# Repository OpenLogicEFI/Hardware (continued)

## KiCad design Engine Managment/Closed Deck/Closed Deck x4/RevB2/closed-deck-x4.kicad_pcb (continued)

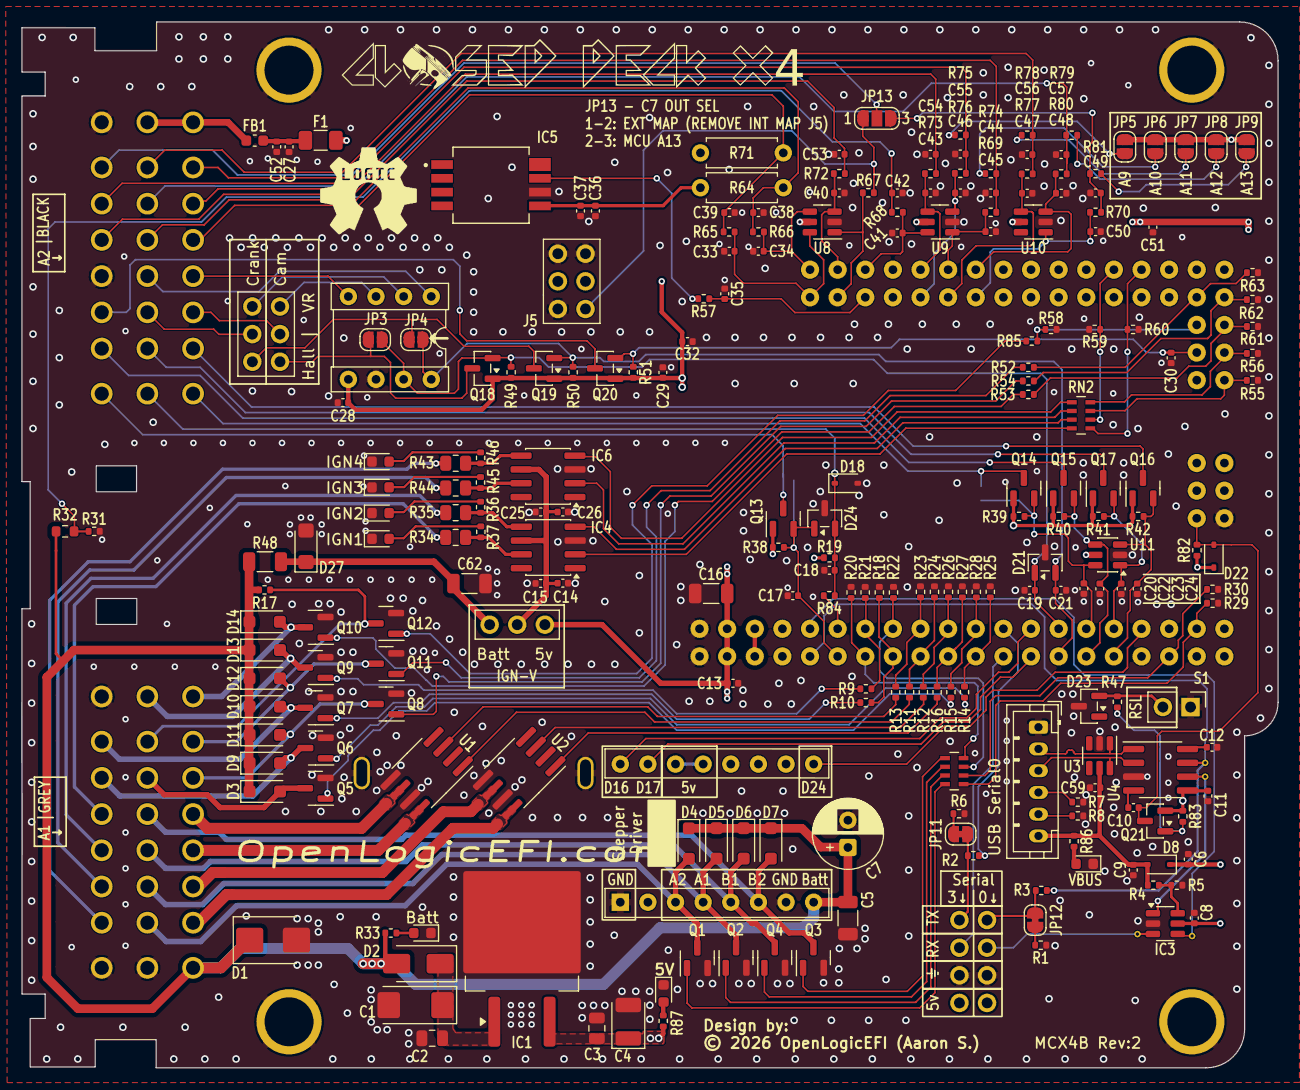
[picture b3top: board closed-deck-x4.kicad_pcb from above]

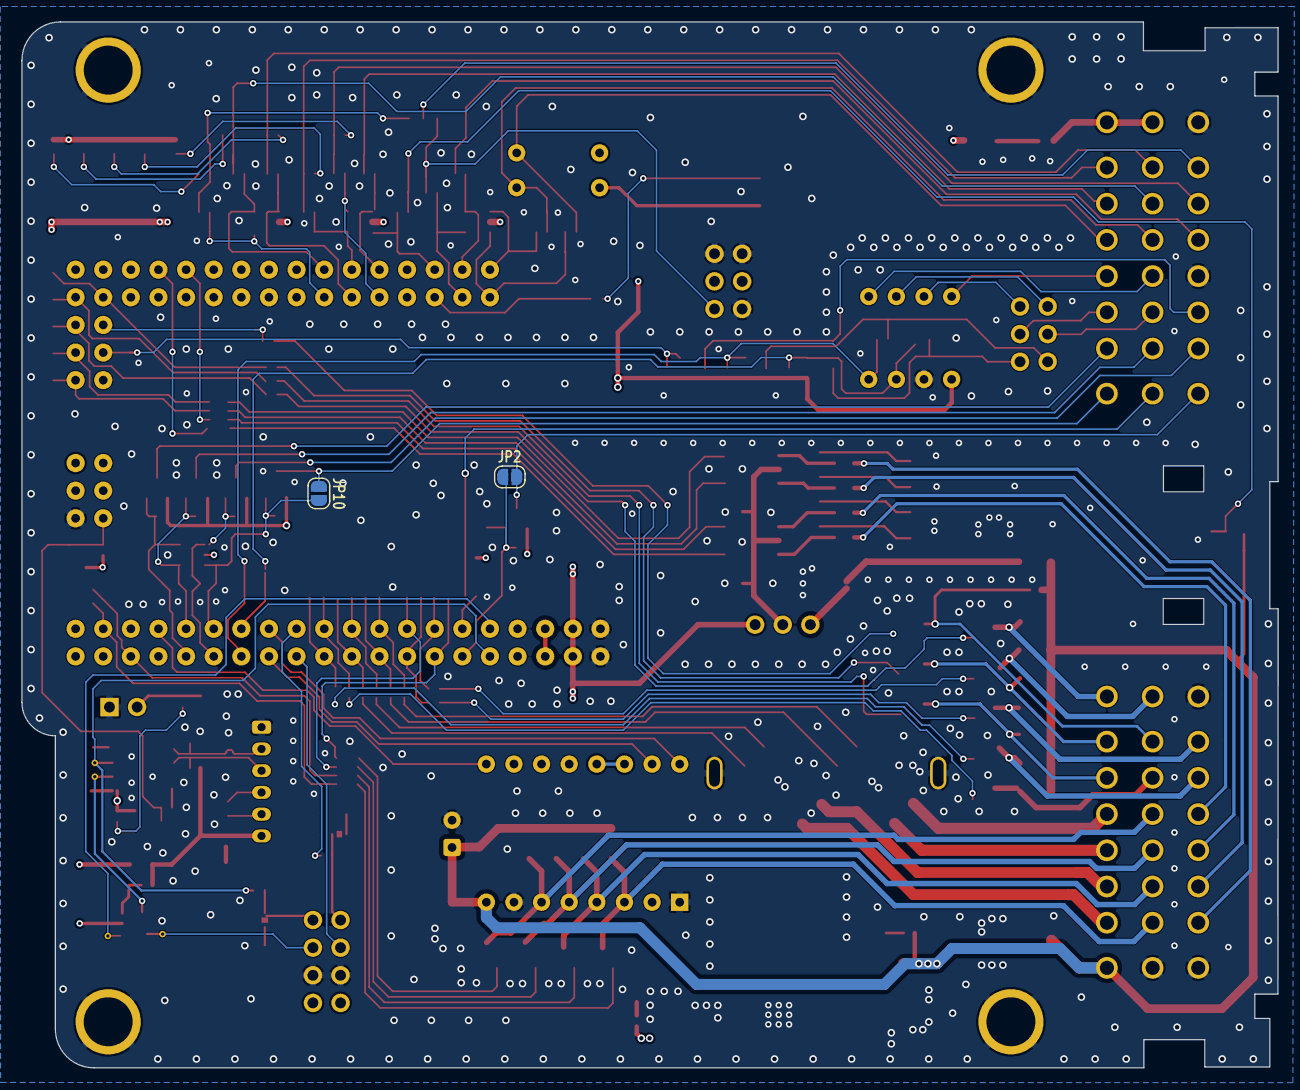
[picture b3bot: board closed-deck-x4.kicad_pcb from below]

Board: 4 copper layers, 115.5 x 96.2 mm, 243 parts (2 on the bottom side), 158 nets.

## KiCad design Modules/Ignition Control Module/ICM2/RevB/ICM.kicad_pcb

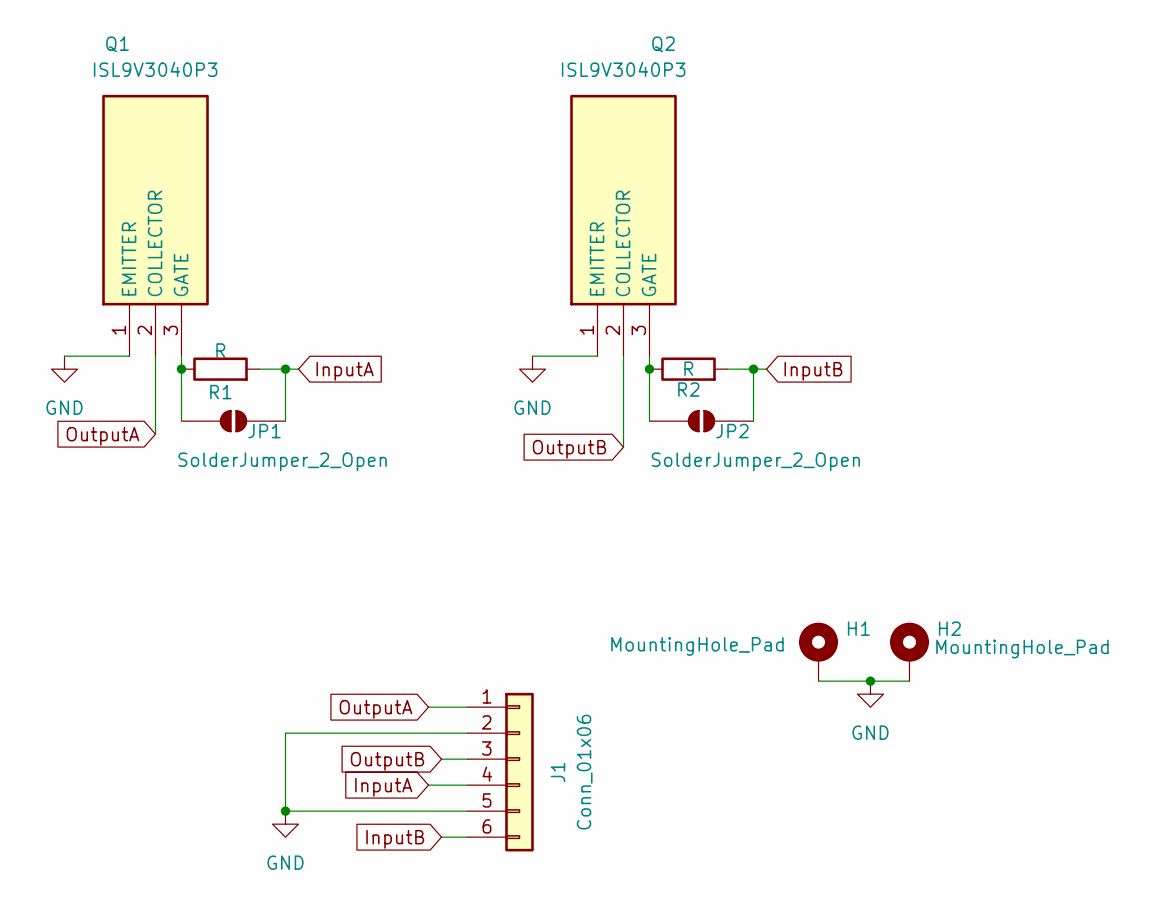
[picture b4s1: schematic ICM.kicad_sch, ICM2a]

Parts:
H1, H2: MountingHole_Pad; MountingHole_3.2mm_M3_DIN965_Pad_TopBottom
J1: Conn_01x06; Molex_Mini-Fit_Jr_5569-06A2_2x03_P4.20mm_Horizontal
JP1, JP2: SolderJumper_2_Open; SolderJumper-2_P1.3mm_Bridged_RoundedPad1.0x1.5mm
Q1, Q2: ISL9V3040P3; TO-252-2-frontThermalOnly; Manufacturer_Part_Number ISL9V3040P3; Mouser Part Number 512-ISL9V3040P3
R1, R2: R; R_Axial_DIN0207_L6.3mm_D2.5mm_P10.16mm_Horizontal

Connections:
GND: H1.1 (1_1), H2.1 (1_1), J1.2, J1.5, Q1.1 (EMITTER), Q2.1 (EMITTER)
InputA: J1.4, JP1.2 (B), R1.2
InputB: J1.6, JP2.2 (B), R2.2
unnamed: JP1.1 (A), Q1.3 (GATE), R1.1
unnamed: JP2.1 (A), Q2.3 (GATE), R2.1
OutputA: J1.1, Q1.2 (COLLECTOR)
OutputB: J1.3, Q2.2 (COLLECTOR)

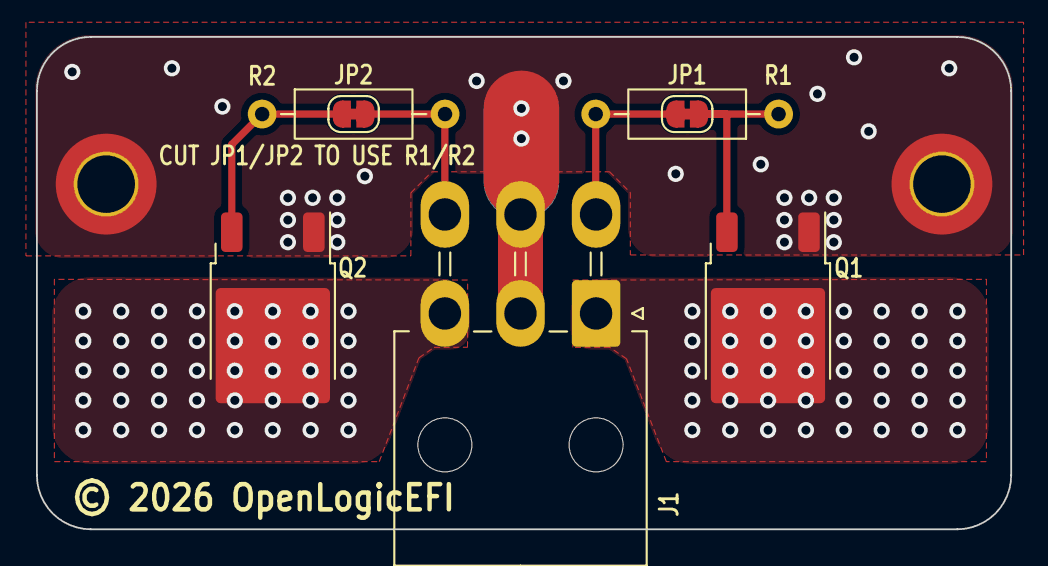
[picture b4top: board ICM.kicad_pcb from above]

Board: 2 copper layers, 54.1 x 27.4 mm, 9 parts (0 on the bottom side), 7 nets.

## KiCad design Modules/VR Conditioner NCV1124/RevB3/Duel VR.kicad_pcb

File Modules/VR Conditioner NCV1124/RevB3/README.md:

# VR Conditioner
Based on the NCV1124
RevB3

Changes:
*Layout improvements

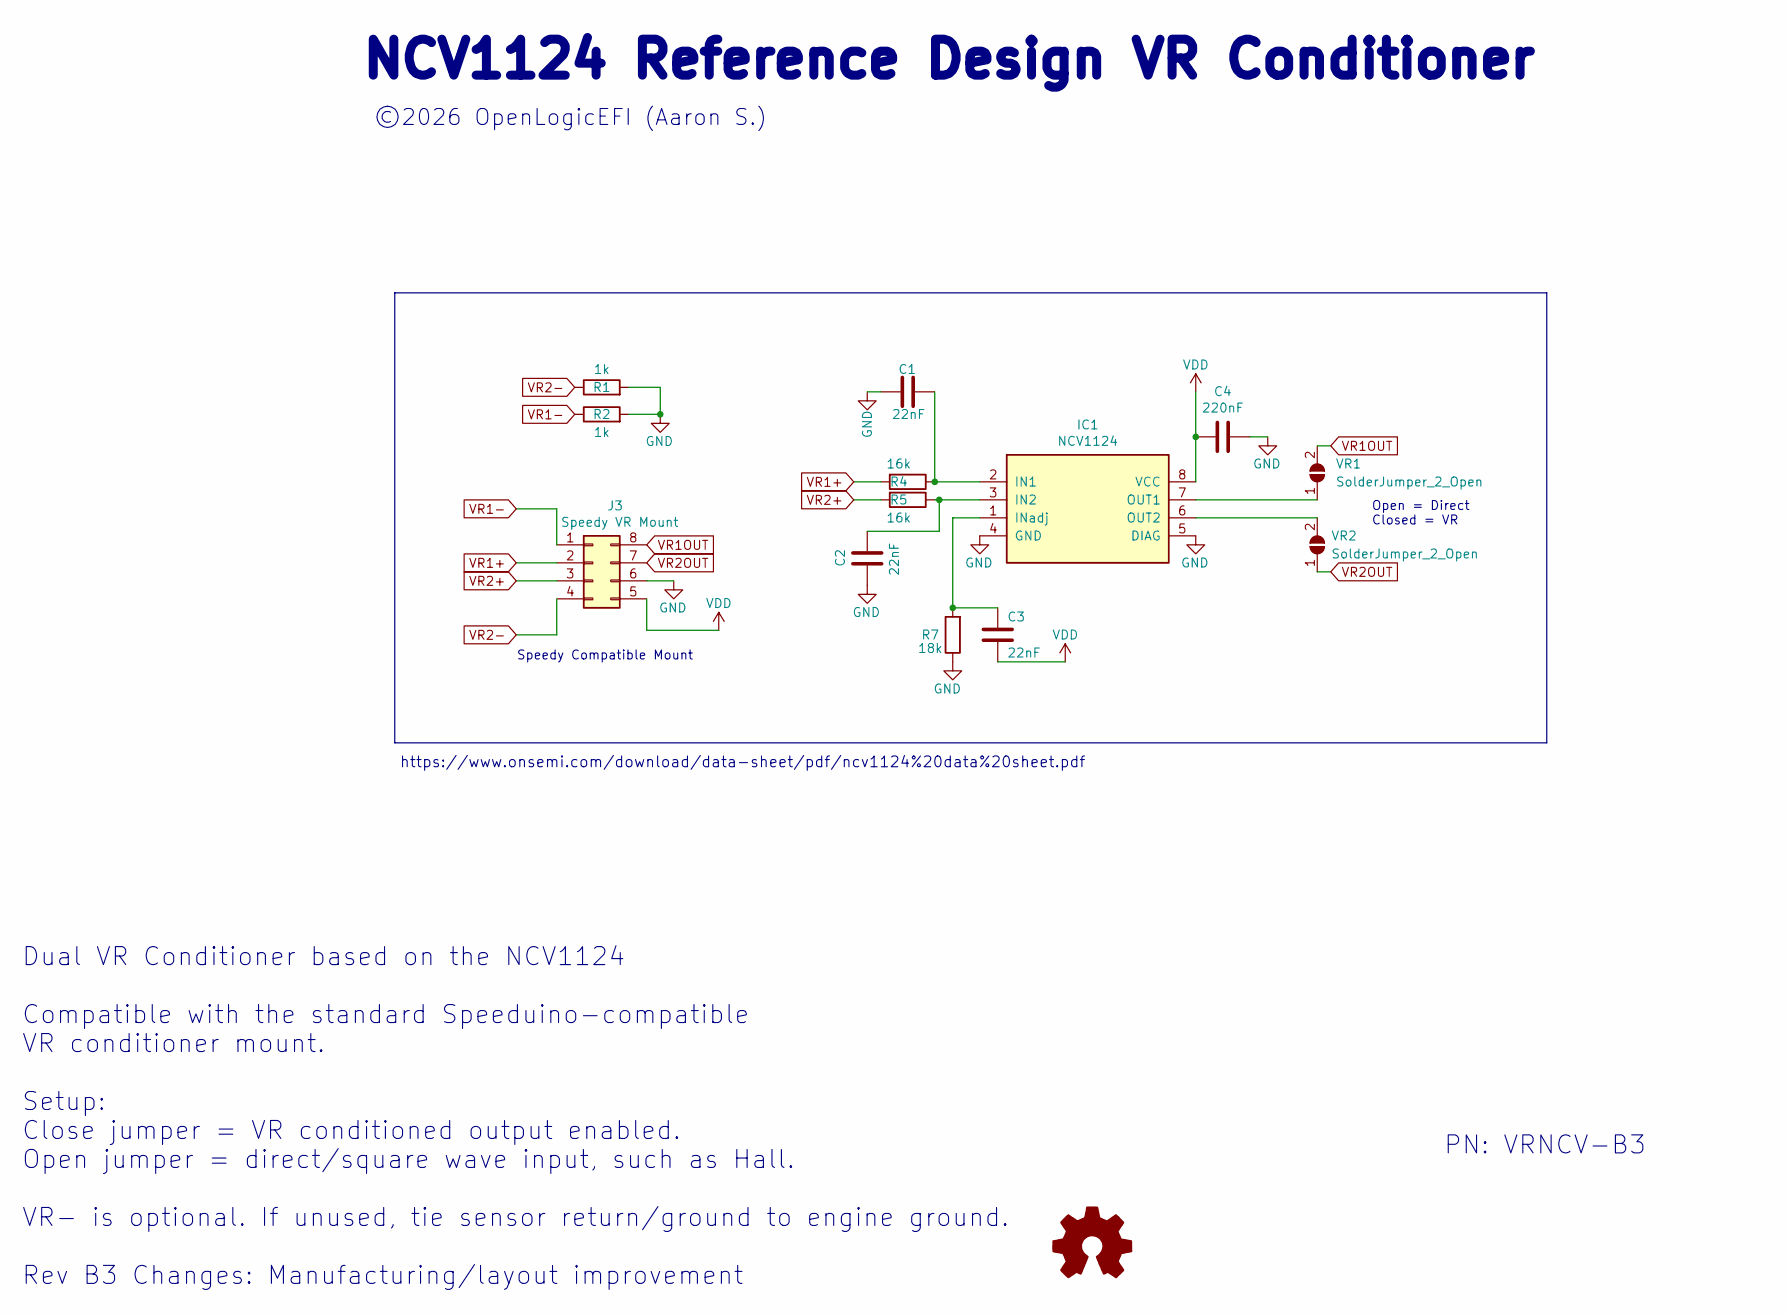
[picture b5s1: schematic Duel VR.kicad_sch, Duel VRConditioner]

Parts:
C1, C2, C3: 22nF; C_0603_1608Metric; LCSC C21122
C4: 220nF; C_0603_1608Metric; LCSC C21120
G1: Logo_Open_Hardware_Small; SpeeduinoCompatible-14mm
IC1: NCV1124; SO-8_3.9x4.9mm_P1.27mm
J3: Speedy VR Mount; DIP-8_W7.62mm_Socket_VRConditioner
R1, R2: 1k; R_1206_3216Metric; LCSC C4410
R4, R5: 16k; R_1210_3225Metric; LCSC C3013274
R7: 18k; R_0603_1608Metric; LCSC C25810
VR1, VR2: SolderJumper_2_Open; SolderJumper-2_P1.3mm_Open_RoundedPad1.0x1.5mm

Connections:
GND: C1.1, C2.2, C4.2, IC1.4 (GND), IC1.5 (DIAG), J3.6, R1.2, R2.2, R7.1
unnamed: C1.2, IC1.2 (IN1), R4.1
unnamed: C2.1, IC1.3 (IN2), R5.1
unnamed: C3.1, IC1.1 (INadj), R7.2
unnamed: IC1.7 (OUT1), VR1.1 (A)
unnamed: IC1.6 (OUT2), VR2.2 (B)
VDD: C3.2, C4.1, IC1.8 (VCC), J3.5
VR1+: J3.2, R4.2
VR1-: J3.1, R2.1
VR1OUT: J3.8, VR1.2 (B)
VR2+: J3.3, R5.2
VR2-: J3.4, R1.1
VR2OUT: J3.7, VR2.1 (A)

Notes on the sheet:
https://www.onsemi.com/download/data-sheet/pdf/ncv1124%20data%20sheet.pdf
Dual VR Conditioner based on the NCV1124 Compatible with the standard Speeduino-compatible VR conditioner mount. Setup: Close jumper = VR conditioned output enabled. Open jumper = direct/square wave input, such as Hall. VR- is optional. If unused, tie sensor return/ground to engine ground. Rev B3 C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
NCV1124 Reference Design VR Conditioner
©2026 OpenLogicEFI (Aaron S.)
Open = Direct Closed = VR
Speedy Compatible Mount
PN: VRNCV-B3

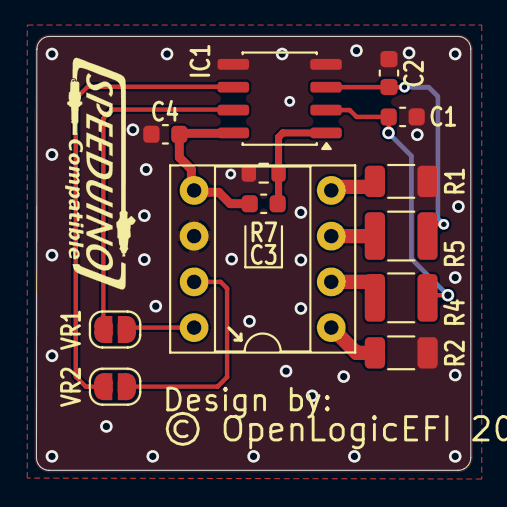
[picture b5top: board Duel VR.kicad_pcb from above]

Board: 2 copper layers, 24.1 x 24.1 mm, 14 parts (0 on the bottom side), 13 nets.

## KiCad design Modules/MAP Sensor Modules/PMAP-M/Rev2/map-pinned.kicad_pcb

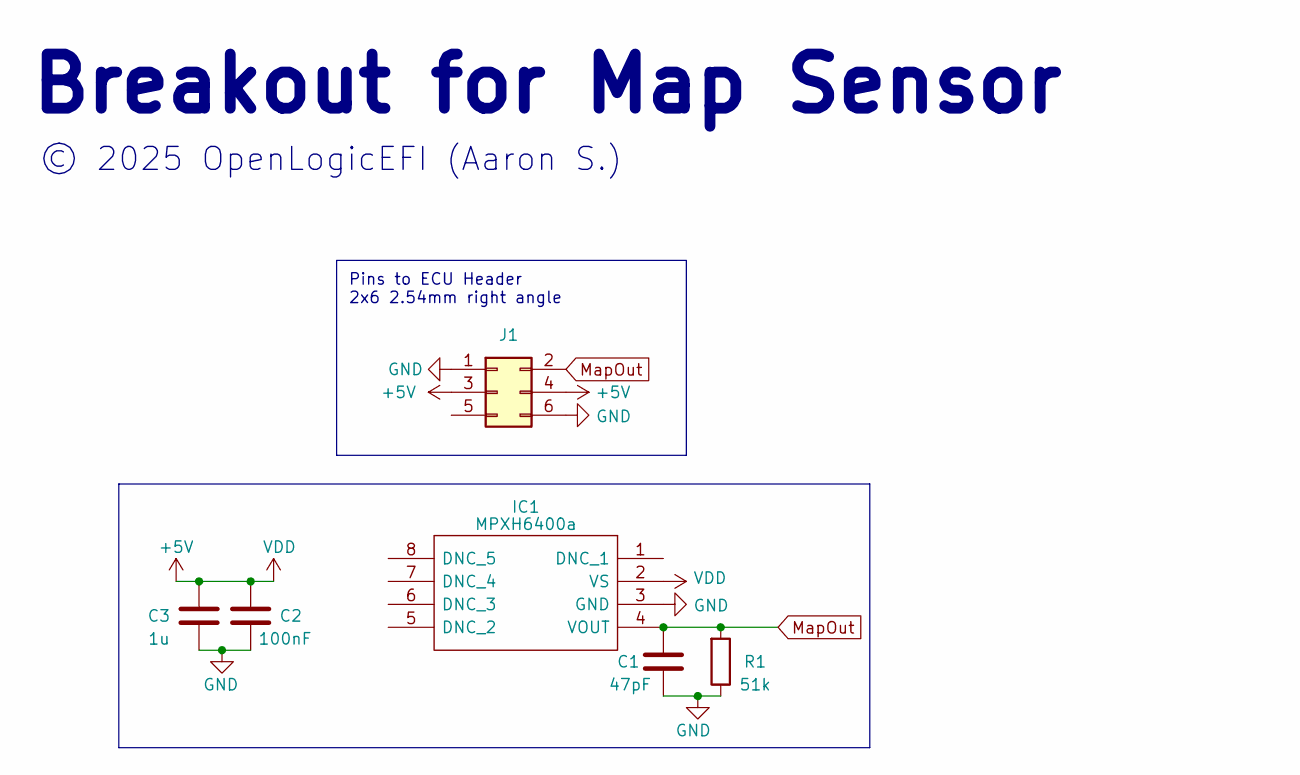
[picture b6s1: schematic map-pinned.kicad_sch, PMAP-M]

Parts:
C1: 47pF; C_0402_1005Metric; Manufacture Part Number 0402CG470J500NT; LCSC C1567
C2: 100nF; C_0402_1005Metric; Manufacture Part Number CL05B104KO5NNNC; LCSC C1525
C3: 1u; C_0805_2012Metric; Manufacture Part Number CL21B105KBFNNNE; LCSC C28323
IC1: MPXH6400a; MPXHxxx_Handsoldering
J1: Conn_02x03_Odd_Even; PinHeader_2x03_P2.54mm_Horizontal
R1: 51k; R_0402_1005Metric; Manufacture Part Number 0402WGF5102TCE; LCSC C25794

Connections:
+5V: C2.1, C3.1, IC1.2 (VS), J1.3, J1.4
GND: C1.2, C2.2, C3.2, IC1.3 (GND), J1.1, J1.6, R1.1
MapOut: C1.1, IC1.4 (VOUT), J1.2, R1.2

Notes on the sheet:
Pins to ECU Header 2x6 2.54mm right angle
© 2025 OpenLogicEFI (Aaron S.)
Breakout for Map Sensor

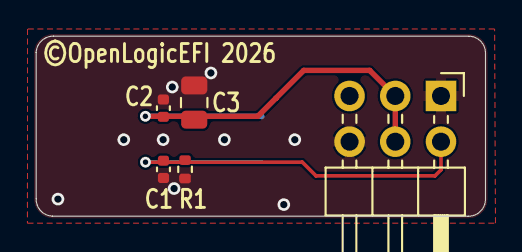
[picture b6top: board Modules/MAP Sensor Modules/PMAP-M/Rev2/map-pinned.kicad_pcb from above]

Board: 2 copper layers, 25.0 x 10.0 mm, 6 parts (1 on the bottom side), 3 nets.

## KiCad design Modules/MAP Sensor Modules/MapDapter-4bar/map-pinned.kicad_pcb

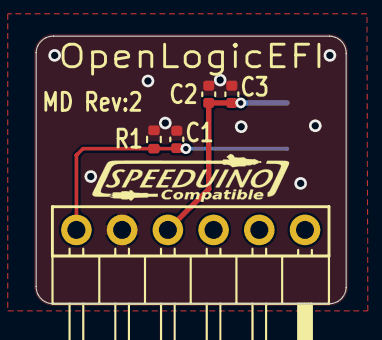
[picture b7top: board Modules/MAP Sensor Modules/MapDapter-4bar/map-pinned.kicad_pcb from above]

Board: 2 copper layers, 17.2 x 14.9 mm, 6 parts (1 on the bottom side), 3 nets.

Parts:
C1: 47pF; C_0402_1005Metric
C2: 100nF; C_0402_1005Metric
C3: 1u; C_0402_1005Metric
IC1: MPXH6400a; MPXHxxx_Handsoldering
J2: Conn_01x06; MapDapter_1x06_P2.54mm_Horizontal
R1: 51k; R_0402_1005Metric

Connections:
+5V: C2.1, C3.1, IC1.2 (VS), J2.4
GND: C1.2, C2.2, C3.2, IC1.3 (GND), J2.5, R1.1
MapOut: C1.1, IC1.4 (VOUT), J2.6, R1.2

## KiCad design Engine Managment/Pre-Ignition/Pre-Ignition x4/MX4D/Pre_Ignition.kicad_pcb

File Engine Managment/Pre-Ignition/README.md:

# Pre-Ignition

Pre-Ignition is a hardware shield designed to use an Arduino Mega as the central microcontroller unit (MCU), thereby enabling it to operate as a standalone engine management system. This functionality is achieved when the shield is coupled with compatible firmware from an open-source project called Speeduino, developed by Josh Stewart.

www.OpenLogicEFI.com

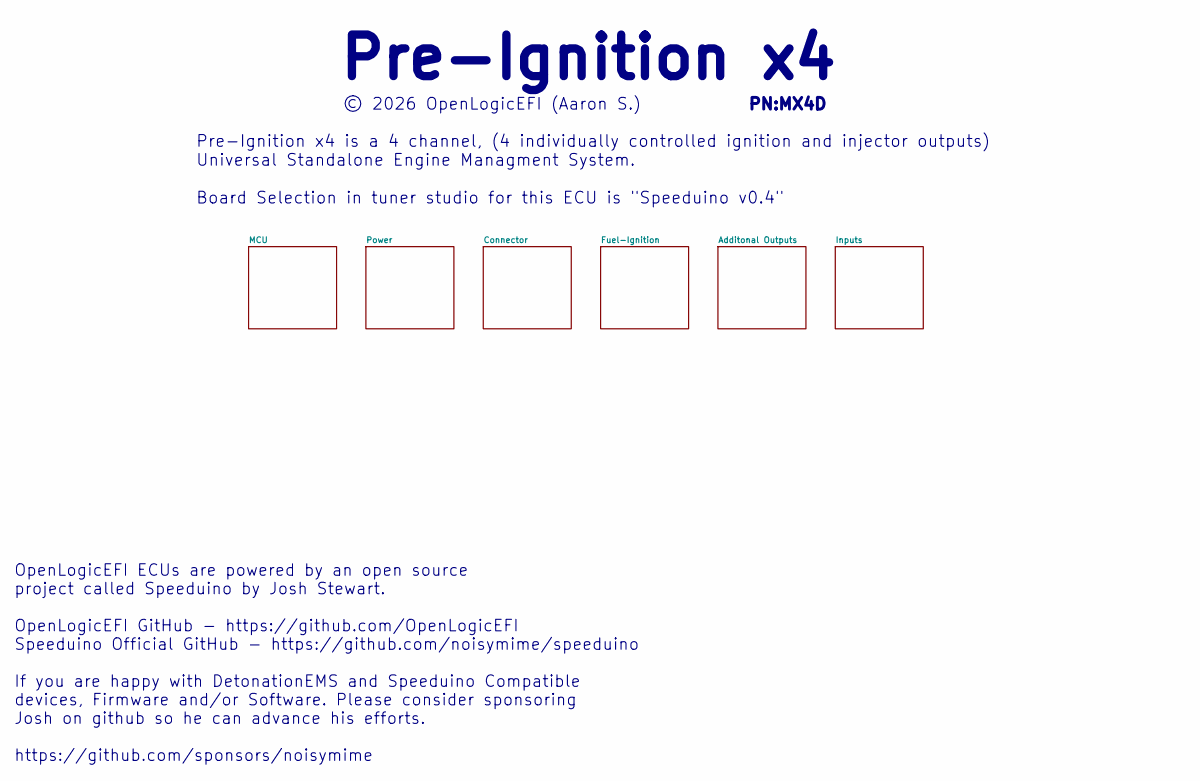
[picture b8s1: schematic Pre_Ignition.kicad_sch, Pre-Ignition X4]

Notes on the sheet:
Pre-Ignition x4 is a 4 channel, (4 individually controlled ignition and injector outputs) Universal Standalone Engine Managment System. Board Selection in tuner studio for this ECU is "Speeduino v0.4"
© 2026 OpenLogicEFI (Aaron S.)
Pre-Ignition x4
OpenLogicEFI ECUs are powered by an open source project called Speeduino by Josh Stewart. OpenLogicEFI GitHub - https://github.com/OpenLogicEFI Speeduino Official GitHub - https://github.com/noisymime/speeduino If you are happy with DetonationEMS and Speeduino Compatible devices, Firmware and/or So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
PN:MX4D

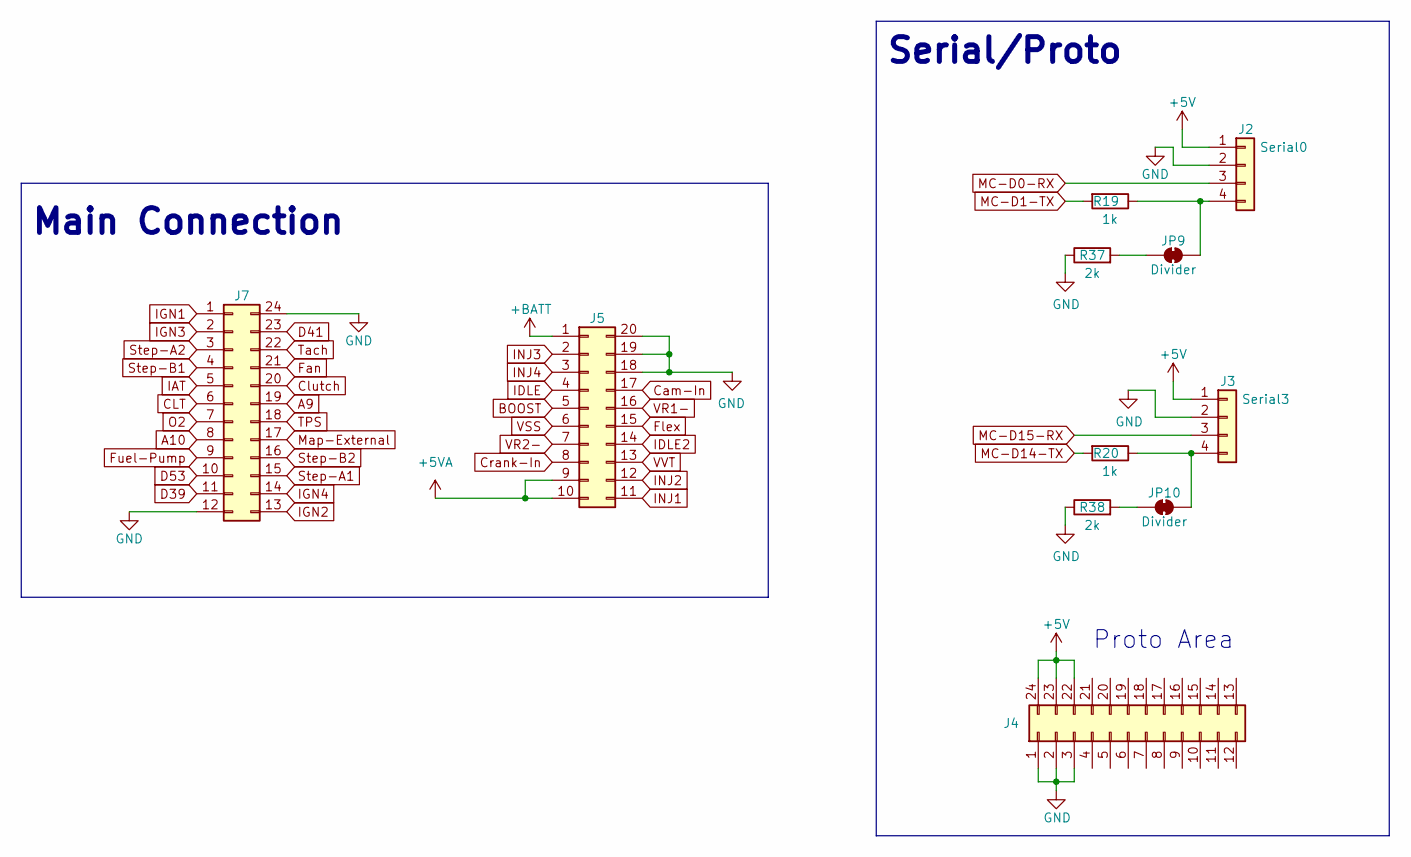
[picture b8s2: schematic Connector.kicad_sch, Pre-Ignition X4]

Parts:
J2: Serial0; 1X4-PROTO
J3: Serial3; 1X4-PROTO
J4: Conn_02x12_Counter_Clockwise; PROTO-3X8-24pin
J5: Conn_02x10_Counter_Clockwise; Molex_Micro-Fit_3.0_43045-2000_2x10_P3.00mm_Horizontal
J7: Conn_02x12_Counter_Clockwise; Molex_Micro-Fit_3.0_43045-2400_2x12_P3.00mm_Horizontal
JP9, JP10: Divider; SolderJumper-2_P1.3mm_Bridged_RoundedPad1.0x1.5mm
R19, R20: 1k; R_0402_1005Metric; Manufacture Part Number 0402WGF1001TCE; LCSC C11702
R37, R38: 2k; R_0603_1608Metric; LCSC C22975

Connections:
+5V: J2.1, J3.1, J4.22, J4.23, J4.24; also elsewhere on the board
+5VA: J5.9, J5.10; also elsewhere on the board
+BATT: J5.1; also elsewhere on the board
A9: J7.19; also elsewhere on the board
A10: J7.8; also elsewhere on the board
BOOST: J5.5; also elsewhere on the board
CLT: J7.6; also elsewhere on the board
Cam-In: J5.17; also elsewhere on the board
Clutch: J7.20; also elsewhere on the board
Crank-In: J5.8; also elsewhere on the board
D39: J7.11; also elsewhere on the board
D41: J7.23; also elsewhere on the board
D53: J7.10; also elsewhere on the board
Fan: J7.21; also elsewhere on the board
Flex: J5.15; also elsewhere on the board
Fuel-Pump: J7.9; also elsewhere on the board
GND: J2.2, J3.2, J4.1, J4.2, J4.3, J5.18, J5.19, J5.20, J7.12, J7.24, R37.1, R38.1; also elsewhere on the board
IAT: J7.5; also elsewhere on the board
IDLE: J5.4; also elsewhere on the board
IDLE2: J5.14; also elsewhere on the board
IGN1: J7.1; also elsewhere on the board
IGN2: J7.13; also elsewhere on the board
IGN3: J7.2; also elsewhere on the board
IGN4: J7.14; also elsewhere on the board
INJ1: J5.11; also elsewhere on the board
INJ2: J5.12; also elsewhere on the board
INJ3: J5.2; also elsewhere on the board
INJ4: J5.3; also elsewhere on the board
MC-D0-RX: J2.3; also elsewhere on the board
MC-D1-TX: R19.2; also elsewhere on the board
MC-D14-TX: R20.2; also elsewhere on the board
MC-D15-RX: J3.3; also elsewhere on the board
Map-External: J7.17; also elsewhere on the board
unnamed: J2.4, JP9.2 (B), R19.1
unnamed: J3.4, JP10.2 (B), R20.1
unnamed: JP9.1 (A), R37.2
unnamed: JP10.1 (A), R38.2
O2: J7.7; also elsewhere on the board
Step-A1: J7.15; also elsewhere on the board
Step-A2: J7.3; also elsewhere on the board
Step-B1: J7.4; also elsewhere on the board
Step-B2: J7.16; also elsewhere on the board
TPS: J7.18; also elsewhere on the board
Tach: J7.22; also elsewhere on the board
VR1-: J5.16; also elsewhere on the board
VR2-: J5.7; also elsewhere on the board
VSS: J5.6; also elsewhere on the board
VVT: J5.13; also elsewhere on the board

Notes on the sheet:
Proto Area
Serial/Proto
Main Connection

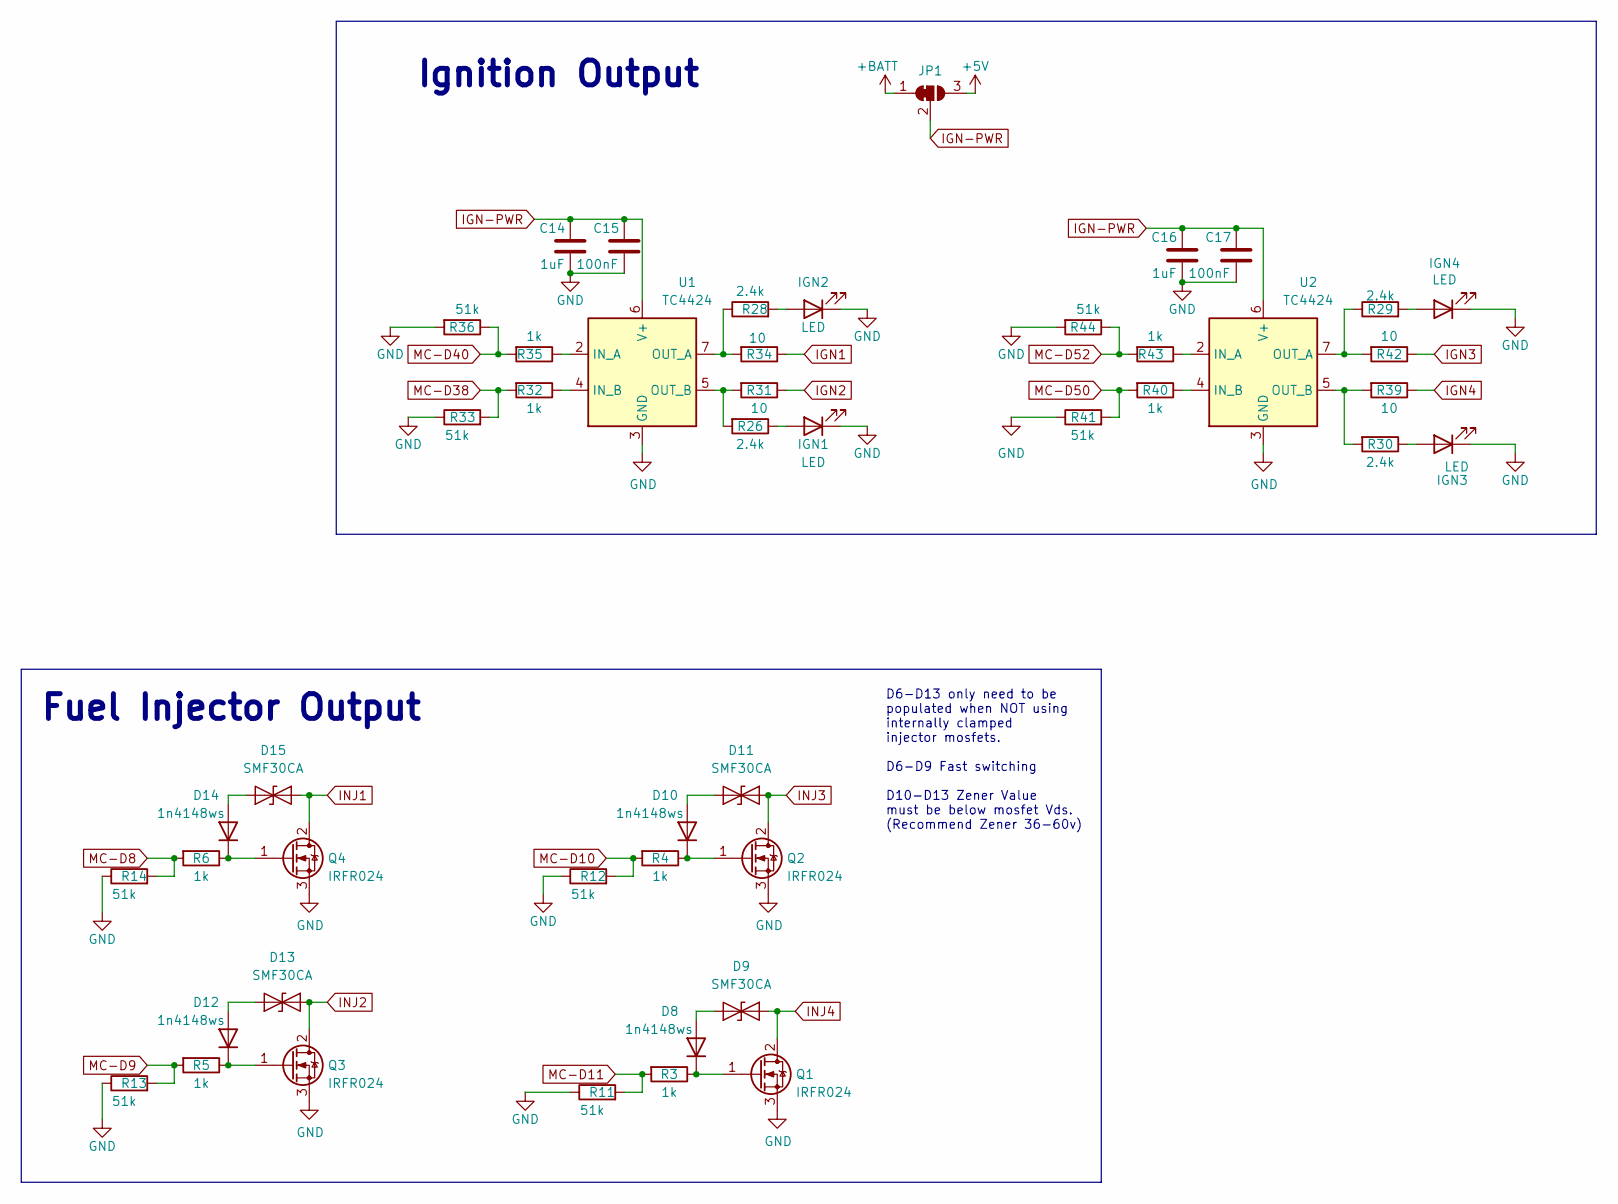
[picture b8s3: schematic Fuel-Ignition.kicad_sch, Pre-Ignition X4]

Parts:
C14, C16: 1uF; C_0603_1608Metric; LCSC C15849
C15, C17: 100nF; C_0603_1608Metric; LCSC C14663
D8, D10, D12, D14: 1n4148ws; D_SOD-323F; LCSC C2128
D9, D11, D13, D15: SMF30CA; D_SOD-123F; LCSC C19077519
IGN1, IGN2, IGN3, IGN4: LED; LED_0603_1608Metric; LCSC C2286
JP1: SolderJumper_3_Bridged12; 1x03_Horizontal_2.54mm
Q1, Q2, Q3, Q4: IRFR024; TO-252-2; LCSC C2583
R3, R4, R5, R6, R32, R35, R40, R43: 1k; R_0402_1005Metric; Manufacture Part Number 0402WGF1001TCE; LCSC C11702
R11, R12, R13, R14, R33, R36, R41, R44: 51k; R_0402_1005Metric; Manufacture Part Number 0402WGF5102TCE; LCSC C25794
R26, R28, R29, R30: 2.4k; C_0603_1608Metric; LCSC C22940
R31, R34, R39, R42: 10; R_1206_3216Metric; LCSC C17903
U1, U2: TC4424; SOIC-8_3.9x4.9mm_P1.27mm; LCSC C2685358

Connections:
+5V: JP1.3 (B); also elsewhere on the board
+BATT: JP1.1 (A); also elsewhere on the board
GND: C14.2, C15.2, C16.2, C17.2, IGN1.1 (K), IGN2.1 (K), IGN3.1 (K), IGN4.1 (K), Q1.3 (S), Q2.3 (S), Q3.3 (S), Q4.3 (S), R11.1, R12.1, R13.1, R14.1, R33.1, R36.2, R41.1, R44.2, U1.3 (GND), U2.3 (GND); also elsewhere on the board
IGN1: R34.1; also elsewhere on the board
IGN2: R31.1; also elsewhere on the board
IGN3: R42.1; also elsewhere on the board
IGN4: R39.1; also elsewhere on the board
IGN-PWR: C14.1, C15.1, C16.1, C17.1, JP1.2 (C), U1.6 (V+), U2.6 (V+)
INJ1: D15.1 (A1), Q4.2 (D); also elsewhere on the board
INJ2: D13.1 (A1), Q3.2 (D); also elsewhere on the board
INJ3: D11.1 (A1), Q2.2 (D); also elsewhere on the board
INJ4: D9.1 (A1), Q1.2 (D); also elsewhere on the board
MC-D8: R6.2, R14.2; also elsewhere on the board
MC-D9: R5.2, R13.2; also elsewhere on the board
MC-D10: R4.2, R12.2; also elsewhere on the board
MC-D11: R3.2, R11.2; also elsewhere on the board
MC-D38: R32.2, R33.2; also elsewhere on the board
MC-D40: R35.2, R36.1; also elsewhere on the board
MC-D50: R40.2, R41.2; also elsewhere on the board
MC-D52: R43.2, R44.1; also elsewhere on the board
unnamed: D8.2 (A), D9.2 (A2)
unnamed: D8.1 (K), Q1.1 (G), R3.1
unnamed: D10.2 (A), D11.2 (A2)
unnamed: D10.1 (K), Q2.1 (G), R4.1
unnamed: D12.2 (A), D13.2 (A2)
unnamed: D12.1 (K), Q3.1 (G), R5.1
unnamed: D14.2 (A), D15.2 (A2)
unnamed: D14.1 (K), Q4.1 (G), R6.1
unnamed: IGN1.2 (A), R26.1
unnamed: IGN2.2 (A), R28.2
unnamed: IGN3.2 (A), R30.1
unnamed: IGN4.2 (A), R29.2
unnamed: R35.1, U1.2 (IN_A)
unnamed: R32.1, U1.4 (IN_B)
unnamed: R28.1, R34.2, U1.7 (OUT_A)
unnamed: R26.2, R31.2, U1.5 (OUT_B)
unnamed: R43.1, U2.2 (IN_A)
unnamed: R40.1, U2.4 (IN_B)
unnamed: R29.1, R42.2, U2.7 (OUT_A)
unnamed: R30.2, R39.2, U2.5 (OUT_B)

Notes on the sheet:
Fuel Injector Output
D6-D13 only need to be populated when NOT using internally clamped injector mosfets. D6-D9 Fast switching D10-D13 Zener Value must be below mosfet Vds. (Recommend Zener 36-60v)
Ignition Output

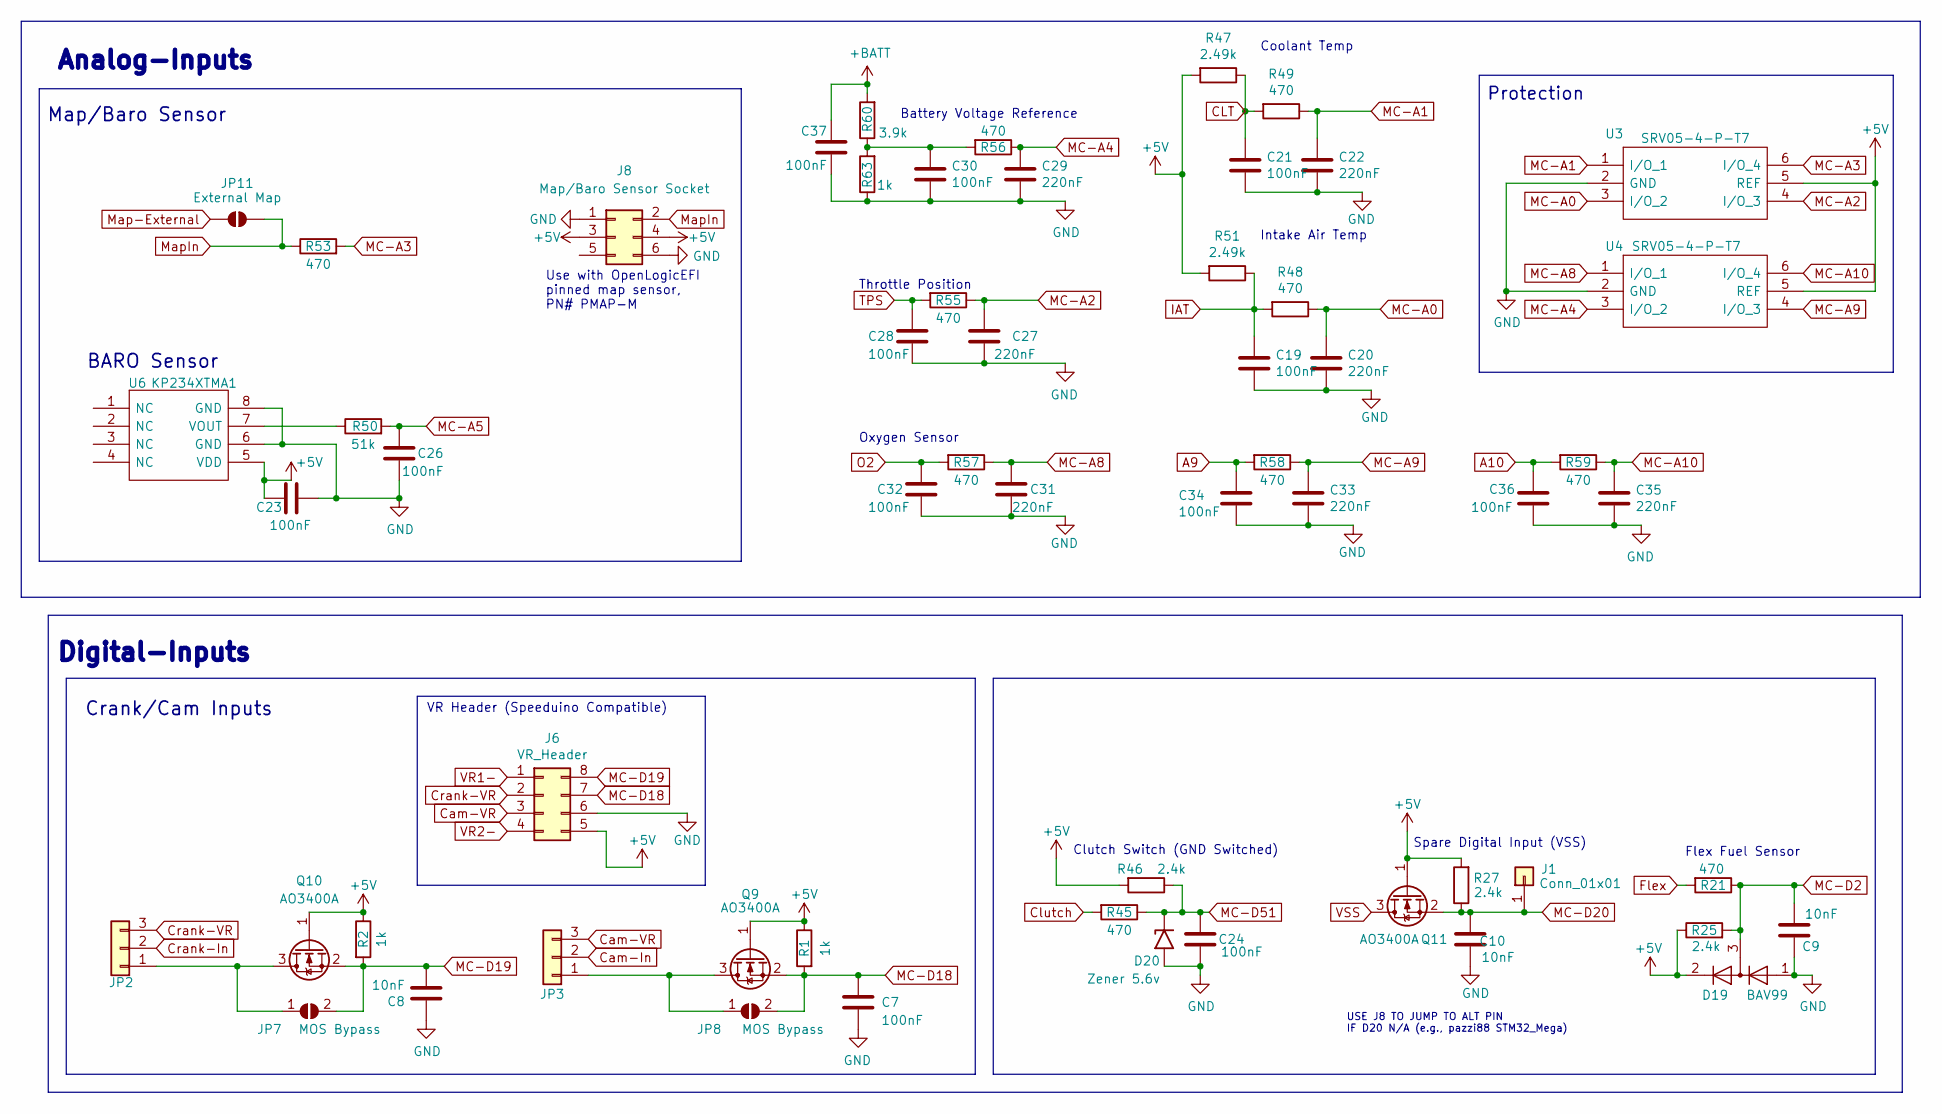
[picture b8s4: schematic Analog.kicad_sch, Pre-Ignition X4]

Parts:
C7, C19, C21, C23, C24, C26, C28, C30, C32, C34, C36, C37: 100nF; C_0603_1608Metric; LCSC C14663
C8, C9, C10: 10nF; C_0603_1608Metric; LCSC C57112
C20, C22, C27, C29, C31, C33, C35: 220nF; C_0603_1608Metric; LCSC C21120
D19: BAV99; SOT-23; LCSC C2500
D20: Zener 5.6v; D_SOD-323; Manufacture Part Number MM3Z5V6; LCSC C19077456
J1: Conn_01x01; PinSocket_1x01_P2.54mm_Vertical
J6: VR_Header; Socket_VRConditioner_Corrected
J8: Map/Baro Sensor Socket; PinSocket_2x03_P2.54mm_Vertical
JP2, JP3: Conn_01x03; 1x03-Proto
JP7, JP8: MOS Bypass; SolderJumper-2_P1.3mm_Open_RoundedPad1.0x1.5mm
JP11: External Map; SolderJumper-2_P1.3mm_Open_RoundedPad1.0x1.5mm
Q9, Q10, Q11: AO3400A; SOT-23; LCSC C20917
R1, R2, R63: 1k; R_0402_1005Metric; Manufacture Part Number 0402WGF1001TCE; LCSC C11702
R21, R45, R48, R49, R53, R55, R56, R57, R58, R59: 470; R_0603_1608Metric; LCSC C23179
R25: 2.4k; C_0603_1608Metric; LCSC C22940
R27, R46: 2.4k; C_0603_1608Metric; Manufacture Part Number 0402WGF1001TCE; LCSC C22940
R47, R51: 2.49k; R_Axial_DIN0207_L6.3mm_D2.5mm_P7.62mm_Horizontal
R50: 51k; R_0402_1005Metric; Manufacture Part Number 0402WGF5102TCE; LCSC C25794
R60: 3.9k; R_0603_1608Metric; LCSC C23018
U3, U4: SRV05-4-P-T7; SOT-23-6; LCSC C85364
U6: KP234XTMA1; KP234-Handsoldering

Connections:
+5V: C23.2, D19.2 (A), J6.5, J8.3, J8.4, Q9.1 (G), Q10.1 (G), Q11.1 (G), R1.1, R2.1, R25.1, R27.2, R46.2, R47.2, R51.2, U3.5 (REF), U4.5 (REF), U6.5 (VDD); also elsewhere on the board
+BATT: C37.1, R60.2; also elsewhere on the board
A9: C34.1, R58.2; also elsewhere on the board
A10: C36.1, R59.2; also elsewhere on the board
CLT: C21.1, R47.1, R49.2; also elsewhere on the board
Cam-In: JP3.2; also elsewhere on the board
Cam-VR: J6.3, JP3.3
Clutch: R45.2; also elsewhere on the board
Crank-In: JP2.2; also elsewhere on the board
Crank-VR: J6.2, JP2.3
Flex: R21.2; also elsewhere on the board
GND: C7.1, C8.1, C9.2, C10.2, C19.2, C20.2, C21.2, C22.2, C23.1, C24.2, C26.1, C27.2, C28.2, C29.2, C30.2, C31.2, C32.2, C33.2, C34.2, C35.2, C36.2, C37.2, D19.1 (K), D20.2 (A2), J6.6, J8.1, J8.6, R63.1, U3.2 (GND), U4.2 (GND), U6.6 (GND), U6.8 (GND); also elsewhere on the board
IAT: C19.1, R48.2, R51.1; also elsewhere on the board
MC-A0: C20.1, R48.1, U3.3 (I/O_2); also elsewhere on the board
MC-A1: C22.1, R49.1, U3.1 (I/O_1); also elsewhere on the board
MC-A2: C27.1, R55.1, U3.4 (I/O_3); also elsewhere on the board
MC-A3: R53.2, U3.6 (I/O_4); also elsewhere on the board
MC-A4: C29.1, R56.1, U4.3 (I/O_2); also elsewhere on the board
MC-A5: C26.2, R50.2; also elsewhere on the board
MC-A8: C31.1, R57.1, U4.1 (I/O_1); also elsewhere on the board
MC-A9: C33.1, R58.1, U4.4 (I/O_3); also elsewhere on the board
MC-A10: C35.1, R59.1, U4.6 (I/O_4); also elsewhere on the board
MC-D2: C9.1, D19.3 (K), R21.1, R25.2; also elsewhere on the board
MC-D18: C7.2, J6.7, JP8.2 (B), Q9.2 (S), R1.2; also elsewhere on the board
MC-D19: C8.2, J6.8, JP7.2 (B), Q10.2 (S), R2.2; also elsewhere on the board
MC-D20: C10.1, J1.1, Q11.2 (S), R27.1; also elsewhere on the board
MC-D51: C24.1, D20.1 (A1), R45.1, R46.1; also elsewhere on the board
Map-External: JP11.1 (A); also elsewhere on the board
MapIn: J8.2, JP11.2 (B), R53.1
unnamed: C30.1, R56.2, R60.1, R63.2
unnamed: JP2.1, JP7.1 (A), Q10.3 (D)
unnamed: JP3.1, JP8.1 (A), Q9.3 (D)
unnamed: R50.1, U6.7 (VOUT)
O2: C32.1, R57.2; also elsewhere on the board
TPS: C28.1, R55.2; also elsewhere on the board
VR1-: J6.1; also elsewhere on the board
VR2-: J6.4; also elsewhere on the board
VSS: Q11.3 (D); also elsewhere on the board

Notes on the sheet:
Map/Baro Sensor
Throttle Position
Clutch Switch (GND Switched)
Crank/Cam Inputs
Analog-Inputs
Oxygen Sensor
BARO Sensor
Coolant Temp
Intake Air Temp
VR Header (Speeduino Compatible)
Battery Voltage Reference
Spare Digital Input (VSS)
USE J8 TO JUMP TO ALT PIN IF D20 N/A (e.g., pazzi88 STM32_Mega)
Use with OpenLogicEFI pinned map sensor, PN# PMAP-M
Flex Fuel Sensor
Protection
Digital-Inputs
